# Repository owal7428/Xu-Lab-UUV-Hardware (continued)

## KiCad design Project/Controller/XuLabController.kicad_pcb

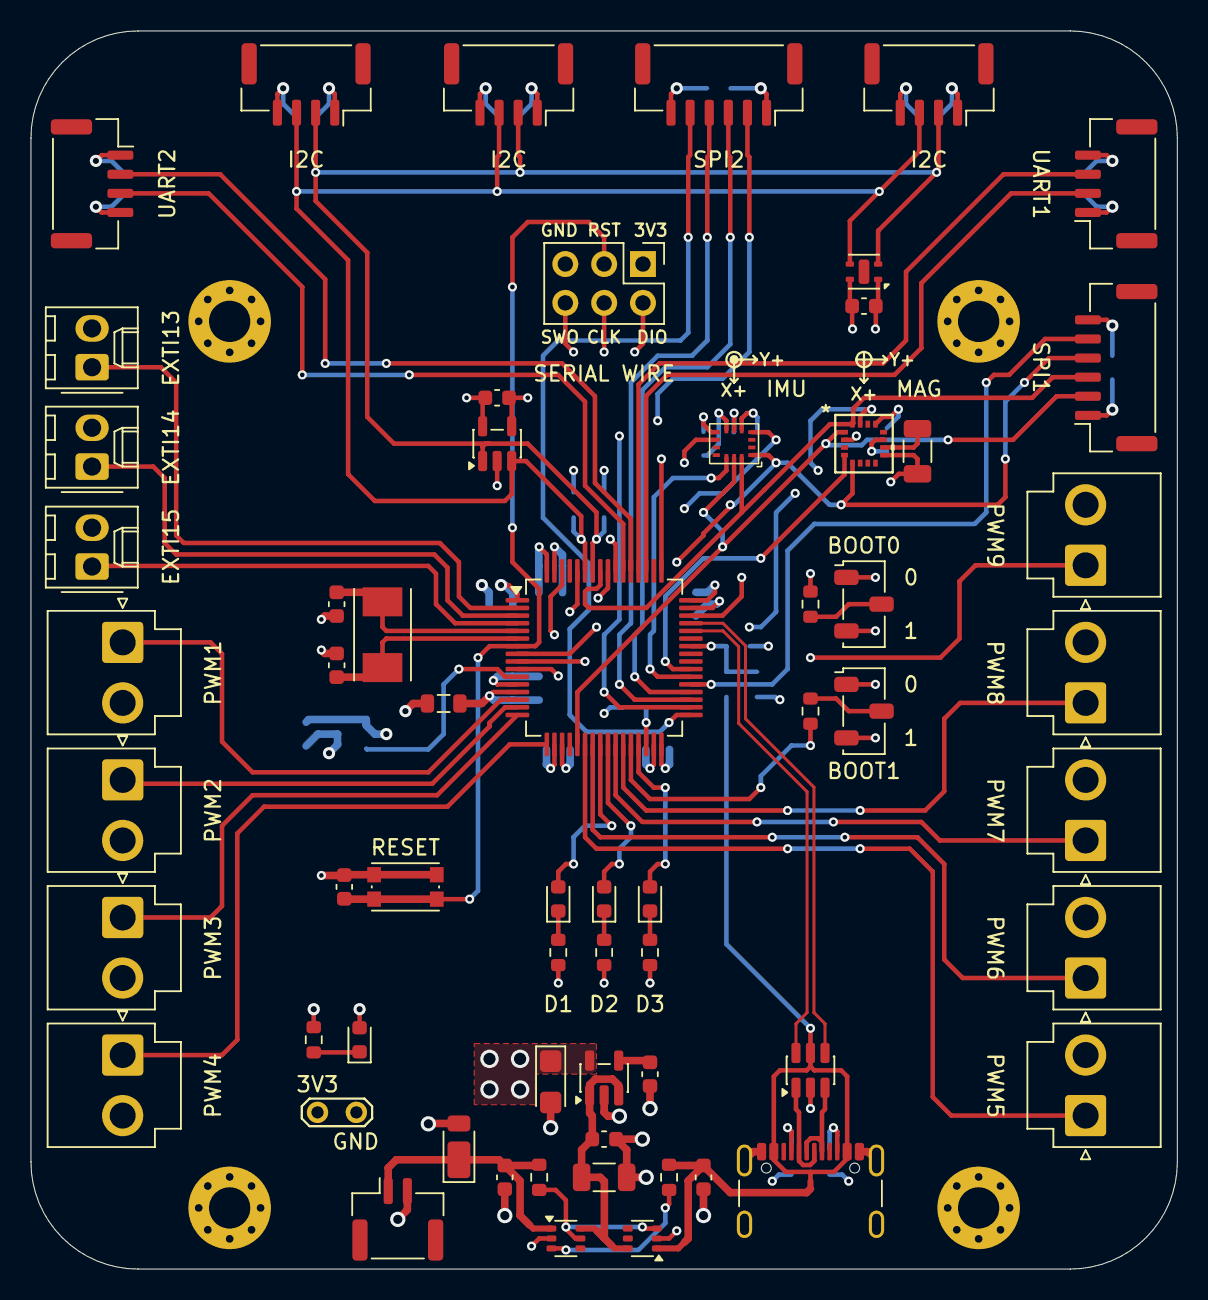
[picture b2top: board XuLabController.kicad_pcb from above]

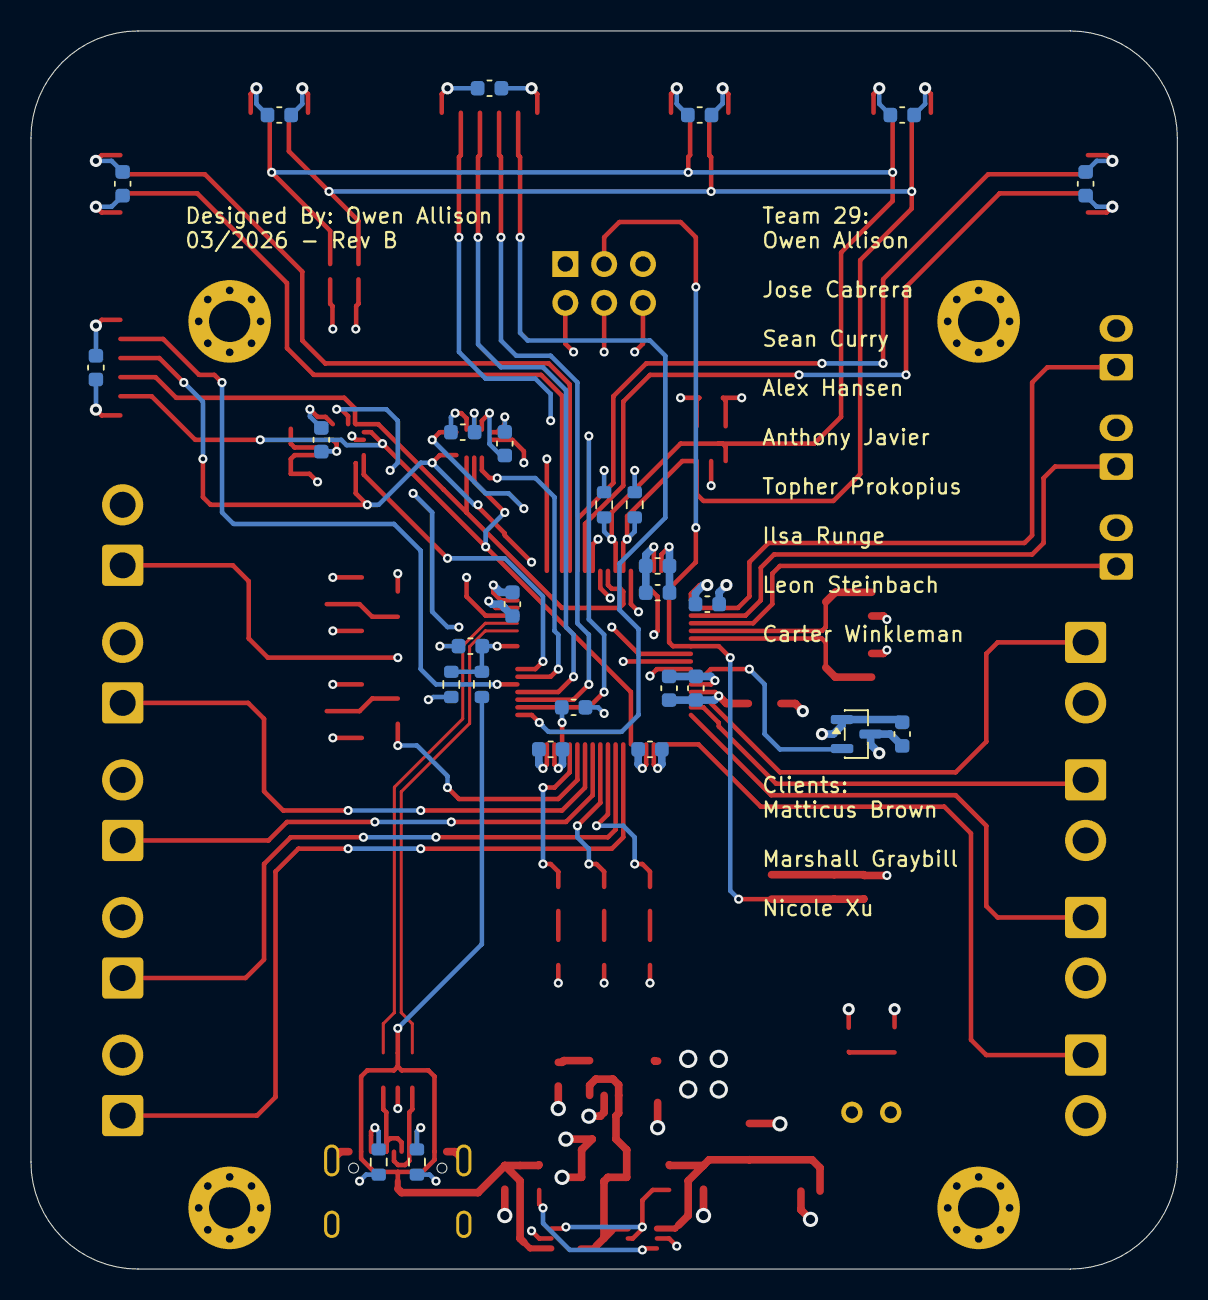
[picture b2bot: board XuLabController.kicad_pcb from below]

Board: 4 copper layers, 75.0 x 81.0 mm, 94 parts (28 on the bottom side), 67 nets.

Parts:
C1, C3, C6, C13, C25: 1uF; C_0603_1608Metric
C2, C26: 10uF; C_1206_3216Metric
C4: 470pF; C_0603_1608Metric
C5: 2.2uF; CP_EIA-3216-18_Kemet-A
C7: 4.7uF; C_0603_1608Metric
C8, C9, C10, C11, C12, C14, C15, C18, C20, C21, C22, C23, C24, C27, C28, C29, C30, C31, C32, C33: 100nF; C_0603_1608Metric
C16, C17: 27pF; C_0603_1608Metric
C19: 2.2uF; C_0603_1608Metric
D1: 5V; D_PowerDI-123
D2: Red; LED_0603_1608Metric
D3: Amber; LED_0603_1608Metric
D4: Green; LED_0603_1608Metric
D5: Blue; LED_0603_1608Metric
FB1: 120 Ohms @ 100 MHz; L_0805_2012Metric
H1, H2, H3, H4: MH; MountingHole_2.7mm_M2.5_Pad_Via
J1: Power; JST_GH_SM02B-GHS-TB_1x02-1MP_P1.25mm_Horizontal
J2: SWD; PinHeader_2x03_P2.54mm_Vertical
J3: USB_C_Receptacle_USB2.0_16P; USB_C_Receptacle_GCT_USB4105-xx-A_16P_TopMnt_Horizontal
J4: Bar30; JST_GH_SM04B-GHS-TB_1x04-1MP_P1.25mm_Horizontal
J5, J6, J7, J8, J9, J10, J11, J12: Servo; JST_VH_B2P-VH_1x02_P3.96mm_Vertical
J13: Thruster; JST_VH_B2P-VH_1x02_P3.96mm_Vertical
J14, J15: I2C; JST_GH_SM04B-GHS-TB_1x04-1MP_P1.25mm_Horizontal
J16: UART1; JST_GH_SM04B-GHS-TB_1x04-1MP_P1.25mm_Horizontal
J17: UART2; JST_GH_SM04B-GHS-TB_1x04-1MP_P1.25mm_Horizontal
J18: SPI1; JST_GH_SM06B-GHS-TB_1x06-1MP_P1.25mm_Horizontal
J19: SPI2; JST_GH_SM06B-GHS-TB_1x06-1MP_P1.25mm_Horizontal
J20, J21, J22: Interrupt; Molex_KK-254_AE-6410-02A_1x02_P2.54mm_Vertical
R1, R2: 47k; R_0603_1608Metric
R3, R8, R9: 330; R_0603_1608Metric
R4, R5: 10k; R_0603_1608Metric
R6, R7: 4k7; R_0603_1608Metric
R10: 100; R_0603_1608Metric
R11: 33k; R_0603_1608Metric
R12, R13: 5k1; R_0603_1608Metric
R14: 82k; R_0603_1608Metric
SW1, SW2: SW_SPDT; Nidec_Copal_CAS-120A
SW3: SW_Push; SW_Push_1P1T_NO_CK_KMR2
TP1: Power; TestPoint_2Pads_Pitch2.54mm_Drill0.8mm
U1, U3: LM66100DCK; SOT-363_SC-70-6
U2: MIC5219-3.3YM5; SOT-23-5
U4: STM32F446RCTx; LQFP-64_10x10mm_P0.5mm
U5: 24AA64-OT; SOT-23-5
U6: USBLC6-2SC6; SOT-23-6
U7: BMI330
U8: MMC5983MA; MMC5983MA_MEM
U9: MCP9700Ax-ETT; SOT-23
U10: SHTC3; Sensirion_DFN-4-1EP_2x2mm_P1mm_EP0.7x1.6mm
Y1: 8MHz; Crystal_SMD_Abracon_ABM7-2Pin_6.0x3.5mm

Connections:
+3.3V: C5.1, C7.1, C8.1, C9.1, C10.1, C11.1, C12.1, C18.1, C21.1, C22.1, C23.1, C24.1, C25.1, C27.1, C28.1, C29.1, C30.1, C31.1, C32.1, C33.1, D2.2 (A), FB1.2, J2.1, J4.1, J14.1, J15.1, J16.1, J17.1, J18.1, J19.1, R6.1, R7.1, SW1.3 (C), SW2.3 (C), TP1.1, U2.5 (OUT), U4.1 (VBAT), U4.19 (VDD), U4.32 (VDD), U4.48 (VDD), U4.64 (VDD), U5.4 (V_{CC}), U7.5 (VDDIO), U7.8 (VDD), U8.2 (VDD), U8.13 (VDDIO), U9.1 (V_{DD}), U10.1 (VDD)
+3.3VA: C13.1, C14.1, FB1.1, U4.13 (VDDA)
/GPIO_EXTI0: U4.8 (PC0), U7.9 (INT2)
/GPIO_EXTI1: U4.9 (PC1), U7.4 (INT1)
/GPIO_EXTI2: U4.10 (PC2), U8.15 (INT)
/GPIO_EXTI13: J20.1, U4.2 (PC13)
/GPIO_EXTI14: J21.1, U4.3 (PC14)
/GPIO_EXTI15: J22.1, U4.4 (PC15)
/I2C1_SCL: J4.2, J14.2, J15.2, R6.2, U4.58 (PB6), U5.1 (SCL), U10.2 (SCL)
/I2C1_SDA: J4.3, J14.3, J15.3, R7.2, U4.59 (PB7), U5.3 (SDA), U10.3 (SDA)
/Microcontroller/BOOT0: R4.2, U4.60 (BOOT0)
/Microcontroller/BOOT1: R5.2, U4.28 (PB2)
/Microcontroller/LED_OUT1: D3.2 (A), U4.24 (PC4)
/Microcontroller/LED_OUT2: D4.2 (A), U4.25 (PC5)
/Microcontroller/LED_OUT3: D5.2 (A), U4.29 (PB10)
/Microcontroller/NRST: C15.1, J2.3, SW3.1, U4.7 (NRST)
/Microcontroller/RCC_IN: C16.1, U4.5 (PH0), Y1.1
/Microcontroller/RCC_OUT: C17.1, U4.6 (PH1), Y1.2
/Microcontroller/SW_CLK: J2.4, U4.49 (PA14)
/Microcontroller/SW_DIO: J2.2, U4.46 (PA13)
/Microcontroller/SW_O: J2.6, U4.55 (PB3)
/Microcontroller/USB_CC1: J3.A5 (CC1), R12.1
/Microcontroller/USB_CC2: J3.B5 (CC2), R13.1
/Microcontroller/USB_D+: U4.45 (PA12), U6.4 (I/O2)
/Microcontroller/USB_D-: U4.44 (PA11), U6.6 (I/O1)
/Microcontroller/USB_VBUS: C20.1, R11.2, R14.1, U4.42 (PA9)
/PWM_1: J5.1, U4.14 (PA0)
/PWM_2: J6.1, U4.15 (PA1)
/PWM_3: J7.1, U4.16 (PA2)
/PWM_4: J8.1, U4.17 (PA3)
/PWM_5: J9.1, U4.22 (PA6)
/PWM_6: J10.1, U4.23 (PA7)
/PWM_7: J11.1, U4.26 (PB0)
/PWM_8: J12.1, U4.27 (PB1)
/PWM_9: J13.1, U4.62 (PB9)
/Power/Status: R1.2, U1.5 (ST), U3.3 (~CE)
/SPI1_CS0: J18.5, U4.37 (PC6)
/SPI1_CS1: U4.38 (PC7), U7.12 (CS)
/SPI1_CS2: U4.39 (PC8), U8.4 (SPI_CS)
/SPI1_MISO: J18.4, U4.56 (PB4), U7.1 (SDO), U8.5 (SPI_SDO)
/SPI1_MOSI: J18.3, U4.57 (PB5), U7.14 (SDI), U8.16 (SDA/SPI_SDI)
/SPI1_SCK: J18.2, U4.21 (PA5), U7.13 (SCK), U8.1 (SCL/SPI_SCK)
/SPI2_MISO: J19.4, U4.35 (PB14)
/SPI2_MOSI: J19.3, U4.36 (PB15)
/SPI2_NSS: J19.5, U4.33 (PB12)
/SPI2_SCK: J19.2, U4.34 (PB13)
/TEMP_OUT: U4.11 (PC3), U9.2 (V_{OUT})
/UART1_RX: J16.3, U4.52 (PC11)
/UART1_TX: J16.2, U4.51 (PC10)
/UART2_RX: J17.3, U4.54 (PD2)
/UART2_TX: J17.2, U4.53 (PC12)
/USB_Power: C6.1, J3.A4 (VBUS), J3.A9 (VBUS), J3.B4 (VBUS), J3.B9 (VBUS), R2.2, R11.1, U3.1 (VIN), U6.5 (VBUS)
GND: C1.2, C2.2, C3.2, C4.2, C5.2, C6.2, C7.2, C8.2, C9.2, C10.2, C11.2, C12.2, C13.2, C14.2, C15.2, C16.2, C17.2, C18.2, C19.2, C20.2, C21.2, C22.2, C23.2, C24.2, C25.2, C26.2, C27.2, C28.2, C29.2, C30.2, C31.2, C32.2, C33.2, D1.2 (A), J1.2, J2.5, J3.A1 (GND), J3.A12 (GND), J3.B1 (GND), J3.B12 (GND), J3.S1 (SHIELD), J4.4, J5.2, J6.2, J7.2, J8.2, J9.2, J10.2, J11.2, J12.2, J13.2, J14.4, J15.4, J16.4, J17.4, J18.6, J19.6, J20.2, J21.2, J22.2, R3.2, R8.2, R9.2, R10.2, R12.2, R13.2, R14.2, SW1.1 (A), SW2.1 (A), SW3.2, TP1.2, U1.2 (GND), U2.2 (GND), U3.2 (GND), U4.12 (VSSA), U4.18 (VSS), U4.31 (VSS), U4.47 (VSS), U4.63 (VSS), U5.2 (V_{SS}), U5.5 (WP), U6.2 (GND), U7.6 (GNDIO), U7.7 (GND), U8.9 (GND), U8.11 (GND), U9.3 (GND), U10.4 (VSS)
unnamed: C1.1, D1.1 (K), J1.1, R1.1, U1.1 (VIN)
unnamed: D2.1 (K), R3.1
unnamed: D3.1 (K), R8.1
unnamed: D4.1 (K), R9.1
unnamed: D5.1 (K), R10.1
unnamed: J3.A6 (D+), J3.B6 (D+), U6.3 (I/O2)
unnamed: J3.A7 (D-), J3.B7 (D-), U6.1 (I/O1)
unnamed: R4.1, SW1.2 (B)
unnamed: R5.1, SW2.2 (B)
unnamed: C2.1, C3.1, U1.6 (VOUT), U2.1 (IN), U2.3 (EN), U3.6 (VOUT)
unnamed: R2.1, U1.3 (~CE)
unnamed: C4.1, U2.4 (BP)
unnamed: C19.1, U4.30 (VCAP_1)
unnamed: C26.1, U8.10 (CAP)

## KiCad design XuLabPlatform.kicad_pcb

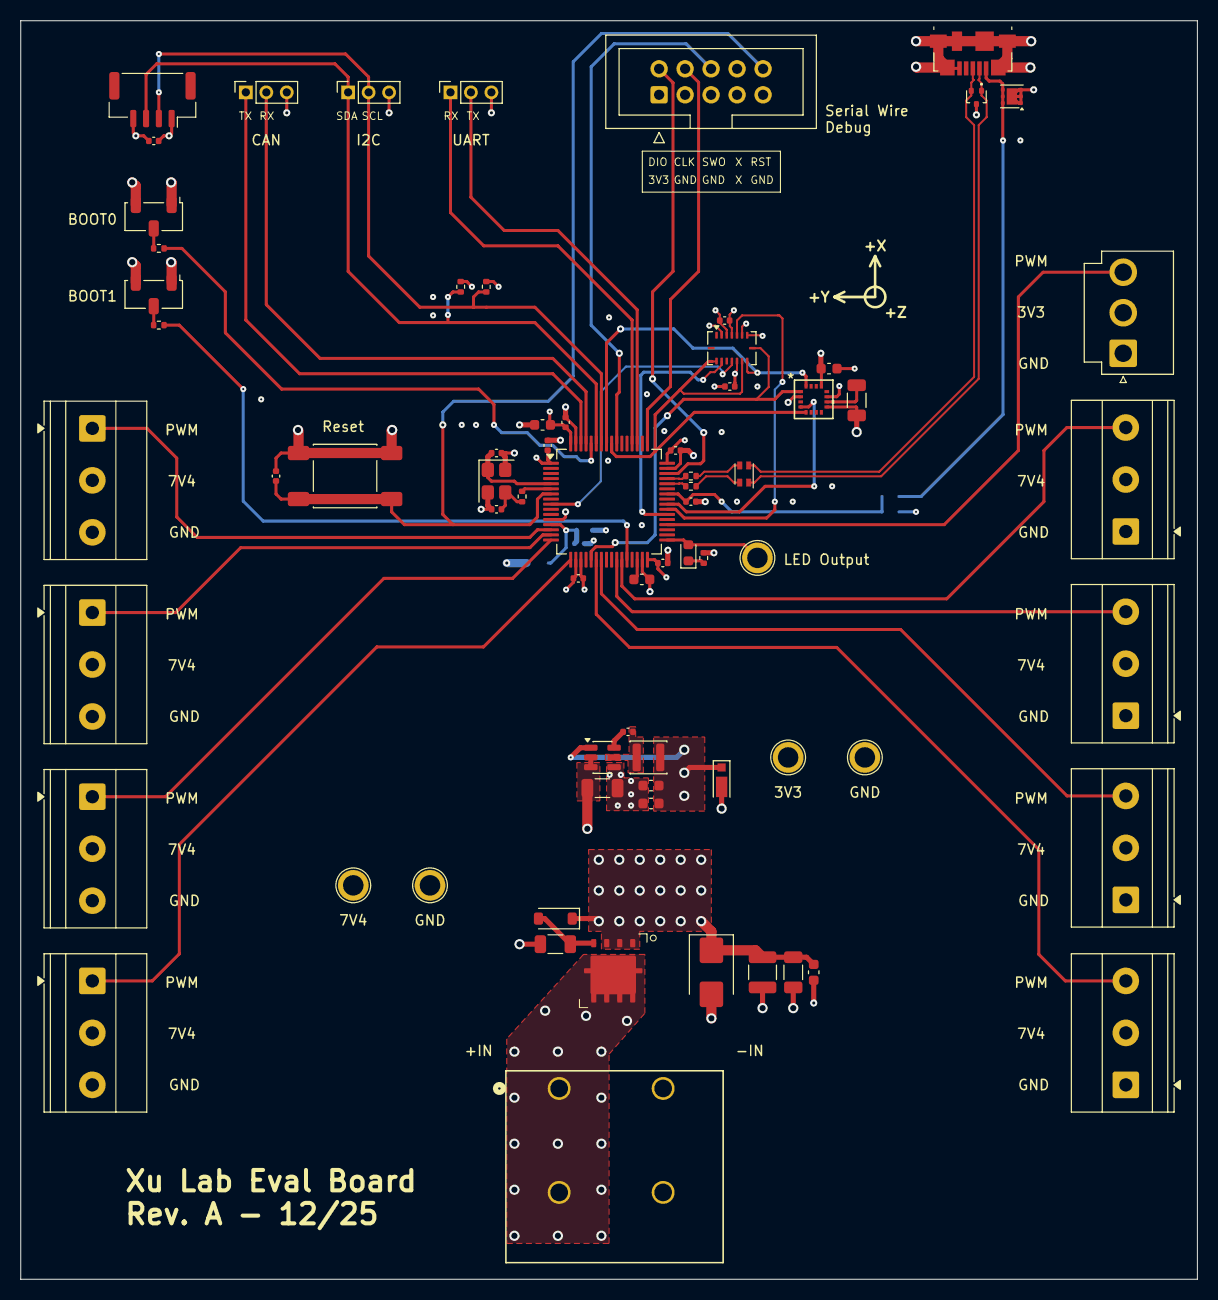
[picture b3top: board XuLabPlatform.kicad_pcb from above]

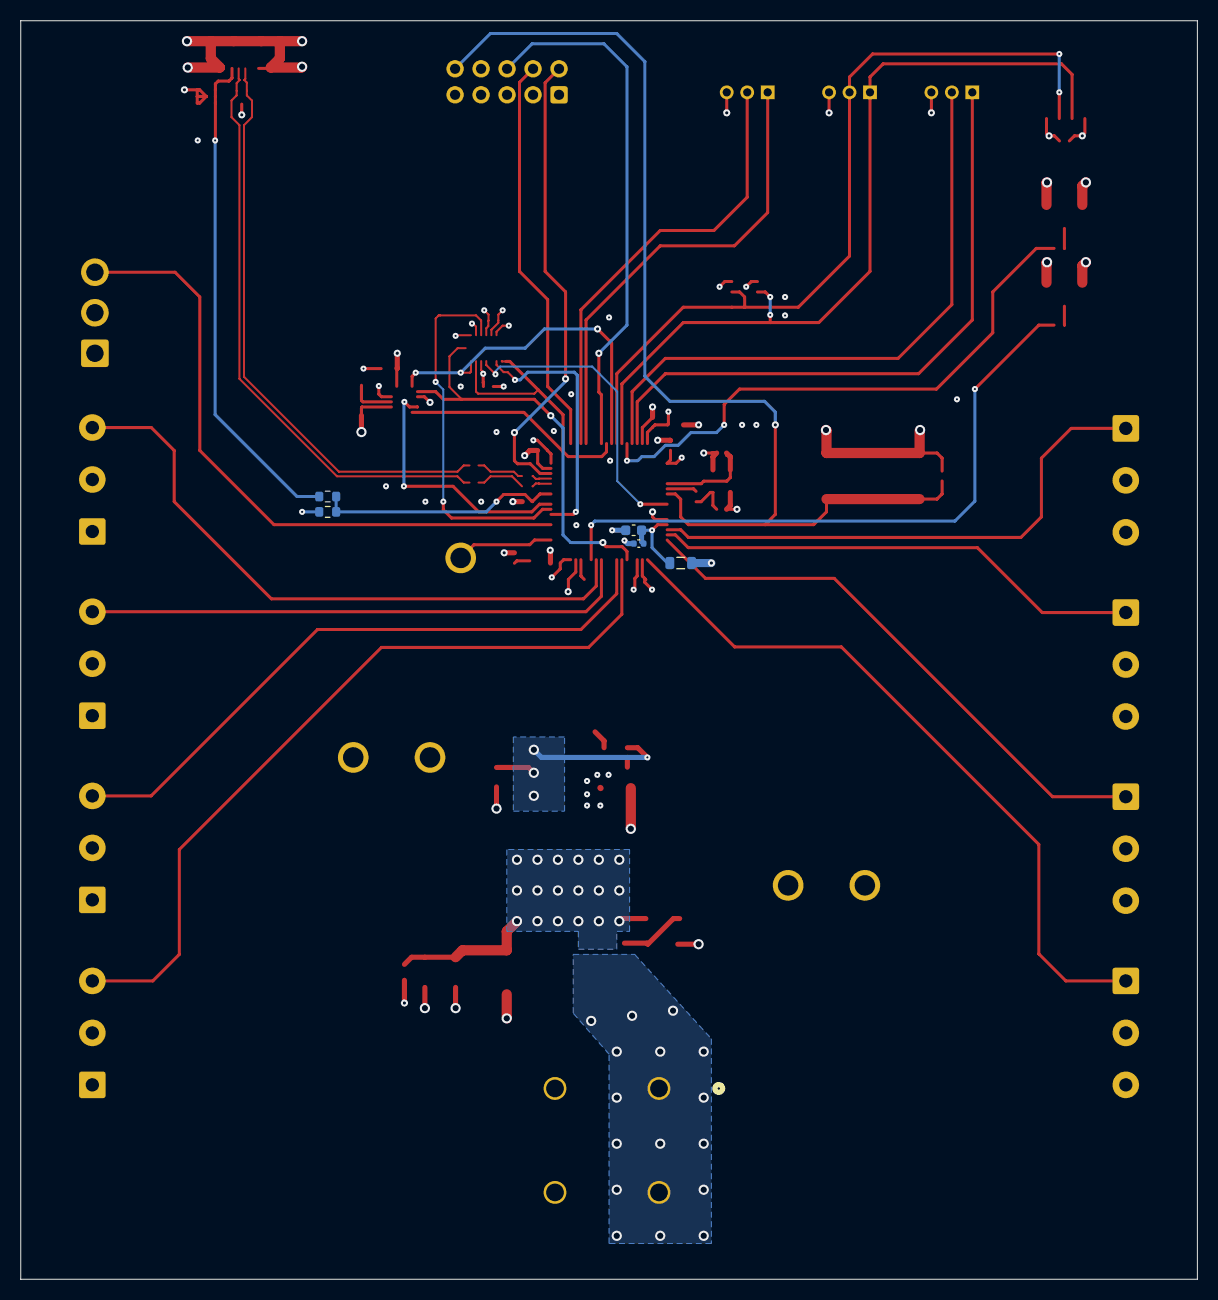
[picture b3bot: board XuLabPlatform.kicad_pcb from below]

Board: 4 copper layers, 115.0 x 123.0 mm, 75 parts (5 on the bottom side), 53 nets.

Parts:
C1: 4.7uF; C_0603_1608Metric
C2, C3, C4, C5, C6, C8, C10, C13, C14, C17, C22, C25: 100nF; C_0402_1005Metric
C7, C15, C20: 1uF; C_0603_1608Metric
C9: 2.2uF; C_0603_1608Metric
C11, C12: 22pF; C_0402_1005Metric
C16, C19, C21: 10uF; C_1206_3216Metric
C18: 100uF; C_1210_3225Metric
C23, C24: 22uF; C_0603_1608Metric
D1: LED; LED_0603_1608Metric
D2: RCLAMP0582B; SOT-416
D3: 12V; D_SOD-123
D4: 7.5V; D_SMB
D5: 3.3V; D_MicroSMP_KA
FB1: 120 Ohms @ 100 MHz; L_0805_2012Metric
FL1: 0805USB-502MLC; L_CommonModeChoke_Coilcraft_0805USB
J1: SWD Connector; IDC-Header_2x05_P2.54mm_Vertical
J2: Conn_01x04; JST_GH_SM04B-GHS-TB_1x04-1MP_P1.25mm_Horizontal
J3: 1986660-2; CONN2_1986660-2_TEC
J4, J5, J6, J7, J8, J9, J10, J11: Servo; TerminalBlock_Phoenix_MKDS-1,5-3-5.08_1x03_P5.08mm_Horizont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
J12: Thruster; JST_VH_B3P-VH_1x03_P3.96mm_Vertical
J13: USB_B_Micro; USB_Micro-B_Molex_47346-0001
J14: CAN; PinSocket_1x03_P2.00mm_Vertical
J15: I2C; PinSocket_1x03_P2.00mm_Vertical
J16: UART; PinSocket_1x03_P2.00mm_Vertical
L1: 3.9uH; L_Pulse_PA4334
Q2: PMOS; SOP-Advance-8
R1, R2: 10k; R_0402_1005Metric
R3: 270; R_0402_1005Metric
R4, R5: 4k7; R_0402_1005Metric
R6, R7: 22; R_0402_1005Metric
R8: 75; R_0402_1005Metric
R9: 100; R_1206_3216Metric
R10: 10k; R_0603_1608Metric
R11: 20k; R_0603_1608Metric
SW1: SW_Push; SW_Push_1P1T_NO_E-Switch_TL3301NxxxxxG
SW2, SW3: SW_SPDT; Nidec_Copal_CAS-120A
TP1, TP2, TP3, TP4, TP5: TestPoint; TestPoint_Plated_Hole_D2.0mm
U1: STM32F446RCTx; LQFP-64_10x10mm_P0.5mm
U2: BMI088; Bosch_LGA-16_4.5x3mm_P0.5mm_LayoutBorder7x1y_ClockwisePinNu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
U3: MMC5983MA; MMC5983MA_MEM
U4: AP63203WU; TSOT-23-6
U5: TVS0500DRV; WSON-6-1EP_2x2mm_P0.65mm_EP1x1.6mm
Y1: 25 MHz; Crystal_SMD_Abracon_ABM8G-4Pin_3.2x2.5mm

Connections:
+3.3V: C1.1, C2.1, C3.1, C4.1, C5.1, C6.1, C13.1, C14.1, C15.1, C17.1, C23.1, C24.1, D5.1 (K), FB1.2, J1.1, J2.1, J12.2, L1.2, R4.1, R5.1, SW2.3 (C), SW3.3 (C), TP2.1, U1.1 (VBAT), U1.19 (VDD), U1.32 (VDD), U1.48 (VDD), U1.64 (VDD), U2.3 (VDD), U2.11 (VDDIO), U3.2 (VDD), U3.13 (VDDIO), U4.1 (FB)
+3.3VA: C7.1, C8.1, FB1.1, U1.13 (VDDA)
+7.4V: C18.1, C19.1, C20.1, C21.1, D3.1 (K), D4.1 (K), J4.2, J5.2, J6.2, J7.2, J8.2, J9.2, J10.2, J11.2, Q2.1 (S), TP1.1, U4.2 (EN), U4.3 (IN)
/CAN1_RX: J14.2, U1.61 (PB8)
/CAN1_TX: J14.1, U1.62 (PB9)
/GPIO_EXTI1: U1.9 (PC1), U2.12 (INT3)
/I2C1_SCL: J2.2, J15.2, R4.2, U1.58 (PB6)
/I2C1_SDA: J2.3, J15.1, R5.2, U1.59 (PB7)
/MCU A/BOOT0: R1.2, U1.60 (BOOT0)
/MCU A/BOOT1: R2.2, U1.28 (PB2)
/MCU A/LED_OUT: D1.2 (A), TP4.1, U1.33 (PB12)
/MCU A/NRST: C10.1, J1.10, SW1.1, U1.7 (NRST)
/MCU A/RCC_IN: C11.1, U1.5 (PH0), Y1.1
/MCU A/RCC_OUT: R3.1, U1.6 (PH1)
/MCU A/SW_CLK: J1.4, U1.49 (PA14)
/MCU A/SW_DIO: J1.2, U1.46 (PA13)
/MCU A/SW_O: J1.6, U1.55 (PB3)
/MCU A/USB_D+: R6.1, U1.45 (PA12)
/MCU A/USB_D-: R7.1, U1.44 (PA11)
/MCU A/USB_D_I+: D2.2 (K2), FL1.2, J13.3 (D+)
/MCU A/USB_D_I-: D2.1 (K1), FL1.1, J13.2 (D-)
/MCU A/USB_D_M+: FL1.3, R6.2
/MCU A/USB_D_M-: FL1.4, R7.2
/MCU A/USB_VBUS: C25.1, R10.2, R11.1, U1.42 (PA9)
/MCU A/USB_VBUS_I: J13.1 (VBUS), R10.1, U5.4 (IN), U5.5 (IN), U5.6 (IN)
/PWM_1: J4.1, U1.14 (PA0)
/PWM_2: J5.1, U1.15 (PA1)
/PWM_3: J6.1, U1.16 (PA2)
/PWM_4: J7.1, U1.17 (PA3)
/PWM_5: J8.3, U1.22 (PA6)
/PWM_6: J9.3, U1.23 (PA7)
/PWM_7: J10.3, U1.26 (PB0)
/PWM_8: J11.3, U1.27 (PB1)
/PWM_9: J12.3, U1.36 (PB15)
/SPI1_CS1: U1.38 (PC7), U2.14 (~CSB1)
/SPI1_CS2: U1.39 (PC8), U2.5 (~CSB2)
/SPI1_CS3: U1.40 (PC9), U3.4 (SPI_CS)
/SPI1_MISO: U1.56 (PB4), U2.10 (SDO2), U2.15 (SDO1), U3.5 (SPI_SDO)
/SPI1_MOSI: U1.57 (PB5), U2.9 (SDI/SDA), U3.16 (SDA/SPI_SDI)
/SPI1_SCK: U1.21 (PA5), U2.8 (SCK/SCL), U3.1 (SCL/SPI_SCK)
/UART_RX: J16.1, U1.52 (PC11)
/UART_TX: J16.2, U1.51 (PC10)
GND: C1.2, C2.2, C3.2, C4.2, C5.2, C6.2, C7.2, C8.2, C9.2, C10.2, C11.2, C12.2, C13.2, C14.2, C15.2, C16.2, C17.2, C18.2, C19.2, C20.2, C21.2, C23.2, C24.2, C25.2, D2.3 (A), D4.2 (A), D5.2 (A), J1.3, J1.5, J1.9, J2.4, J3.2A, J3.2B, J4.3, J5.3, J6.3, J7.3, J8.1, J9.1, J10.1, J11.1, J12.1, J13.5 (GND), J13.6 (Shield), J14.3, J15.3, J16.3, R8.2, R9.2, R11.2, SW1.2, SW2.1 (A), SW3.1 (A), TP3.1, TP5.1, U1.12 (VSSA), U1.18 (VSS), U1.31 (VSS), U1.47 (VSS), U1.63 (VSS), U2.2 (GNDA), U2.4 (GNDA), U2.6 (GNDIO), U2.7 (PS), U3.9 (GND), U3.11 (GND), U4.4 (GND), U5.1 (GND), U5.2 (GND), U5.3 (GND), U5.7 (GND), Y1.2, Y1.4
unnamed: C12.1, R3.2, Y1.3
unnamed: D1.1 (K), R8.1
unnamed: D3.2 (A), Q2.2 (G), R9.1
unnamed: J3.1A, J3.1B, Q2.3 (D)
unnamed: R1.1, SW2.2 (B)
unnamed: R2.1, SW3.2 (B)
unnamed: C9.1, U1.30 (VCAP_1)
unnamed: C16.1, U3.10 (CAP)
unnamed: C22.1, U4.6 (BST)
unnamed: C22.2, L1.1, U4.5 (SW)

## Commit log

2025-10-04 Update gitignore for KiCad files
2025-10-04 Add initial project files
2025-10-06 Add pull request template for better documentation
2025-10-07 Add DS_Store file to gitignore
2025-10-07 Add schematic files for MCUA
2025-10-07 Connect power pins and add decoupling capacitors
2025-10-09 Add circuits to configure reset and boot pins
2025-10-13 Add pin labels
2025-10-15 Add external crystal oscillator
2025-10-15 Add SWD connections
2025-10-15 Add pull up resistors for I2C pins
2025-10-15 Add hierarchical pins for MCU A and update main sheet
2025-10-16 Add hierarchical sheet for attitude and heading sensors
2025-10-16 Add MMC5603NJ symbol and footprint files
2025-10-16 Add 9DoF IMU and magnetometer sensors to sheet
2025-10-17 Add SN74AVC4T774PW library files
2025-10-17 Update MCU A pin configuration with SPI CS and an LED output
2025-10-17 Add sensor connections
2025-10-19 Added Pressure Sensor schematic (Bar30 4-pin: 3.3V, GND, SCL, SDA)
2025-10-19 Add Water Temp Sensor sheet (MCP9808 breakout: 3.3V, GND, SCL, SDA, ALERT)
2025-10-21 Add pressure sensor schematic
2025-10-21 Connect MCU A to sensors
2025-10-22 Rename files using pascal case and update references
2025-10-23 Change IMU to ISM330DHCX and remove SPI level converter
2025-10-23 Remove MMC5603NJ library files
2025-10-23 Add MMC5983MA library files
2025-10-23 Change magnetometer to MMC5983MA
2025-10-24 Change magnetometer interface from I2C to SPI
2025-10-24 Add power schematic sheet
2025-10-27 Add screw terminal power input and symbol
2025-10-27 Add 3v3 buck converter
2025-10-27 Add TVS diodes
2025-10-27 Add connectors for servo power
2025-10-27 Add indicator LED for MCU A
2025-10-27 Add signal outputs for servos and change screw terminal footprints
2025-10-27 Increase power rail decoupling capacitor values
2025-10-28 Add Schottky diode
2025-10-30 Fix duplicate capacitor labels
2025-10-31 Add thruster pin outputs
2025-11-02 Combine servo outputs to 3 pin terminal
2025-11-02 Remove unused I2C pins and add USB
2025-11-02 Add footprints to symbols
2025-11-03 Make USB lines differential
2025-11-03 Add outputs folder to gitignore
2025-11-03 Add test points
2025-11-03 Add surge protection for USB VBUS line
2025-11-03 Add info for pcb sheet
2025-11-03 Fix missing net label for SPI1 SCK
2025-11-03 Switch from variable to fixed 3.3V buck converter
2025-11-13 Add initial PCB layout
2025-11-13 Change ferrite bead with TLV1117LV33 LDO for 3.3VA filtering
2025-11-14 Add footprint and model for TPH1R712MDL1Q
2025-11-14 Add breakout sockets for microcontroller IO lines
2025-11-14 Replace Schottky diode with P-channel mosfet circuit
2025-11-17 Update layout
2025-11-19 Add constraints
2025-11-19 Add ground plane and crystal connections
2025-11-19 Add rest of connections
2025-11-20 Add silkscreen labels
2025-11-20 Set export directories
2025-11-25 Add return vias and modify silkscreen
2025-11-27 Replace zener diode footprints with generics
2025-12-04 Add ferrite bead and decoupling capacitors to analog power input
2025-12-04 Add 3.3 V voltage divider to 5 V VBUS line
2025-12-17 Remove LDO and connect FB to switching output
2025-12-22 Change IMU to BMI088
2025-12-22 Add interchangeable field to BOM
2025-12-25 Change pressure connector from JST-GH-BM04B to JST-GH-SM04B
2026-01-23 Remove test points
2026-01-23 Change servo connectors from screw to JST B3P-VH
2026-01-23 Change crystal capacitors to cheaper model
2026-01-26 Change SWD header to smaller footprint
2026-01-26 Change output peripheral output connectors to Molex PicoBlade
2026-01-27 Remove CAN pins and connector
2026-01-28 Replace EXTI3 with EXTI0
2026-01-28 Add second SPI pins and connector
2026-01-29 Add second UART interface and connector
2026-01-29 Add second I2C connector
2026-01-29 Add second SPI1 connector
2026-01-29 Connect MCU interrupt pins to sensors
2026-02-01 Add extra interrupts and connector
2026-02-01 Add 3.3 V pin to peripheral connectors
2026-02-03 Add 100nF capacitors to connectors
2026-02-04 Move files into controller subfolder
2026-02-04 Remove power schematic from controller board
2026-02-04 Add power board files
2026-02-04 Remove unused library files for controller board
2026-02-04 Re-number components in controller schematic
2026-02-04 Reorganize controller schematic
2026-02-04 Add power input connector to controller schematic
2026-02-04 Add project root folder
2026-02-04 Add 64 kb EEPROM
2026-02-05 Remove battery power from servo PWM connector
2026-02-05 Add LDO to power input for controller board
2026-02-05 Change peripheral connectors to JST GH
2026-02-05 Change USB connector from USB-B Micro to USB-C
2026-02-05 Change USB ESD chip to USBLC6
2026-02-05 Relabel Bar30 I2C connector
2026-03-02 Add ideal diode ORing for power connector and USB power
2026-03-02 Reorganize microcontroller schematic
2026-03-02 Change power connector to JST GH
2026-03-02 Change magnetometer interrupt pin from sensor input to output
2026-03-02 Add power test points
2026-03-02 Change SWD header to 6 pins
2026-03-02 Add 2.7mm M2.5 mounting holes
2026-03-02 Add decoupling capacitor to EEPROM
2026-03-02 Add MCP9700A temperature sensor
2026-03-02 Add two more LEDs and increase LED series resistance
2026-03-02 Reorganize pin layout
2026-03-02 Change resistors in VBUS divider
2026-03-02 Update PCB constraints and defaults
2026-03-02 Remove redundant USB data line series resistors and CM choke
2026-03-02 Re-annotate symbols
2026-03-02 Add initial layout
2026-03-02 Change 0402 footprints to 0603
2026-03-02 Change crystal to 8 MHz
2026-03-02 Change button to smaller footprint
2026-03-02 Move part references to fabrication layers
2026-03-02 Move reset button to open space
2026-03-02 Add silkscreen labeling
2026-03-02 Add trace routing
2026-03-02 Add SHTC3 humidity sensor
2026-03-02 Reformat and remove small silkscreen
2026-03-03 Add client credits
2026-03-03 Add BMI330 library symbols
2026-03-03 Change IMU to BMI330
2026-03-03 Add more power input vias
2026-03-03 Fix connector capacitor alignment
2026-03-04 Add latching circuit schematic
2026-03-06 Remove unused connector symbol
2026-03-06 Move buck converter to separate sheet
2026-03-06 Change power connector to XT60
2026-03-08 Add mounting holes
2026-03-08 Add PowerPAK-SO8 footprint
2026-03-08 Add LM74502 symbol
2026-03-13 Add high-side power switch with LM74502
2026-03-13 Add NCV68061 symbol
2026-03-13 Add ideal diode to battery inputs using NCV68061
2026-03-13 Add indicator LEDs to the batteries
2026-03-18 Add STM32L422KBTx microcontroller
2026-03-18 Connect microcontroller to main enable switch
2026-03-18 Make microcontroller always-on
2026-03-18 Add SPI and I2C connectors for microcontroller
2026-03-18 Add servo connectors
2026-03-18 Reorganize converters
2026-03-19 Change power microcontroller pin ordering
2026-03-19 Add 5V 2A voltage regulator
2026-03-20 Add TPS54627 symbol
2026-03-20 Add 5V 6A voltage regulator
2026-03-20 Add I2C pull-up resistors
2026-03-20 Add INA226 sensors for batteries
2026-03-20 Add more sensors for fin module servos
2026-03-20 Add power flags to battery inputs
2026-03-20 Add TVS diodes to switch and converter outputs
2026-03-20 Add capacitors to servo connectors
2026-03-20 Add converter output connectors
2026-03-20 Increase output converter voltage to ~5.1 V
2026-03-21 Flip XT60 pin connections
2026-03-21 Add capacitors to ideal diode inputs / outputs
2026-03-22 Remove extra capacitor in 5V 2A converter
2026-03-24 Change bulk capacitor to smaller value
2026-03-24 Change connectors to vertical
2026-03-24 Set constraints and pre-defined sizes
2026-03-24 Set stackup to six layers
2026-03-25 Add battery power routing
2026-03-25 Add converter and motor power routing
2026-03-26 Add signal routing
2026-03-26 Add internal 5 and 3.3 V power layers
2026-03-26 Shorten board length
2026-03-26 Add LEDs to the microcontroller
2026-03-26 Add stitching vias
2026-03-26 Add silkscreen
2026-04-23 Update README with power board image
